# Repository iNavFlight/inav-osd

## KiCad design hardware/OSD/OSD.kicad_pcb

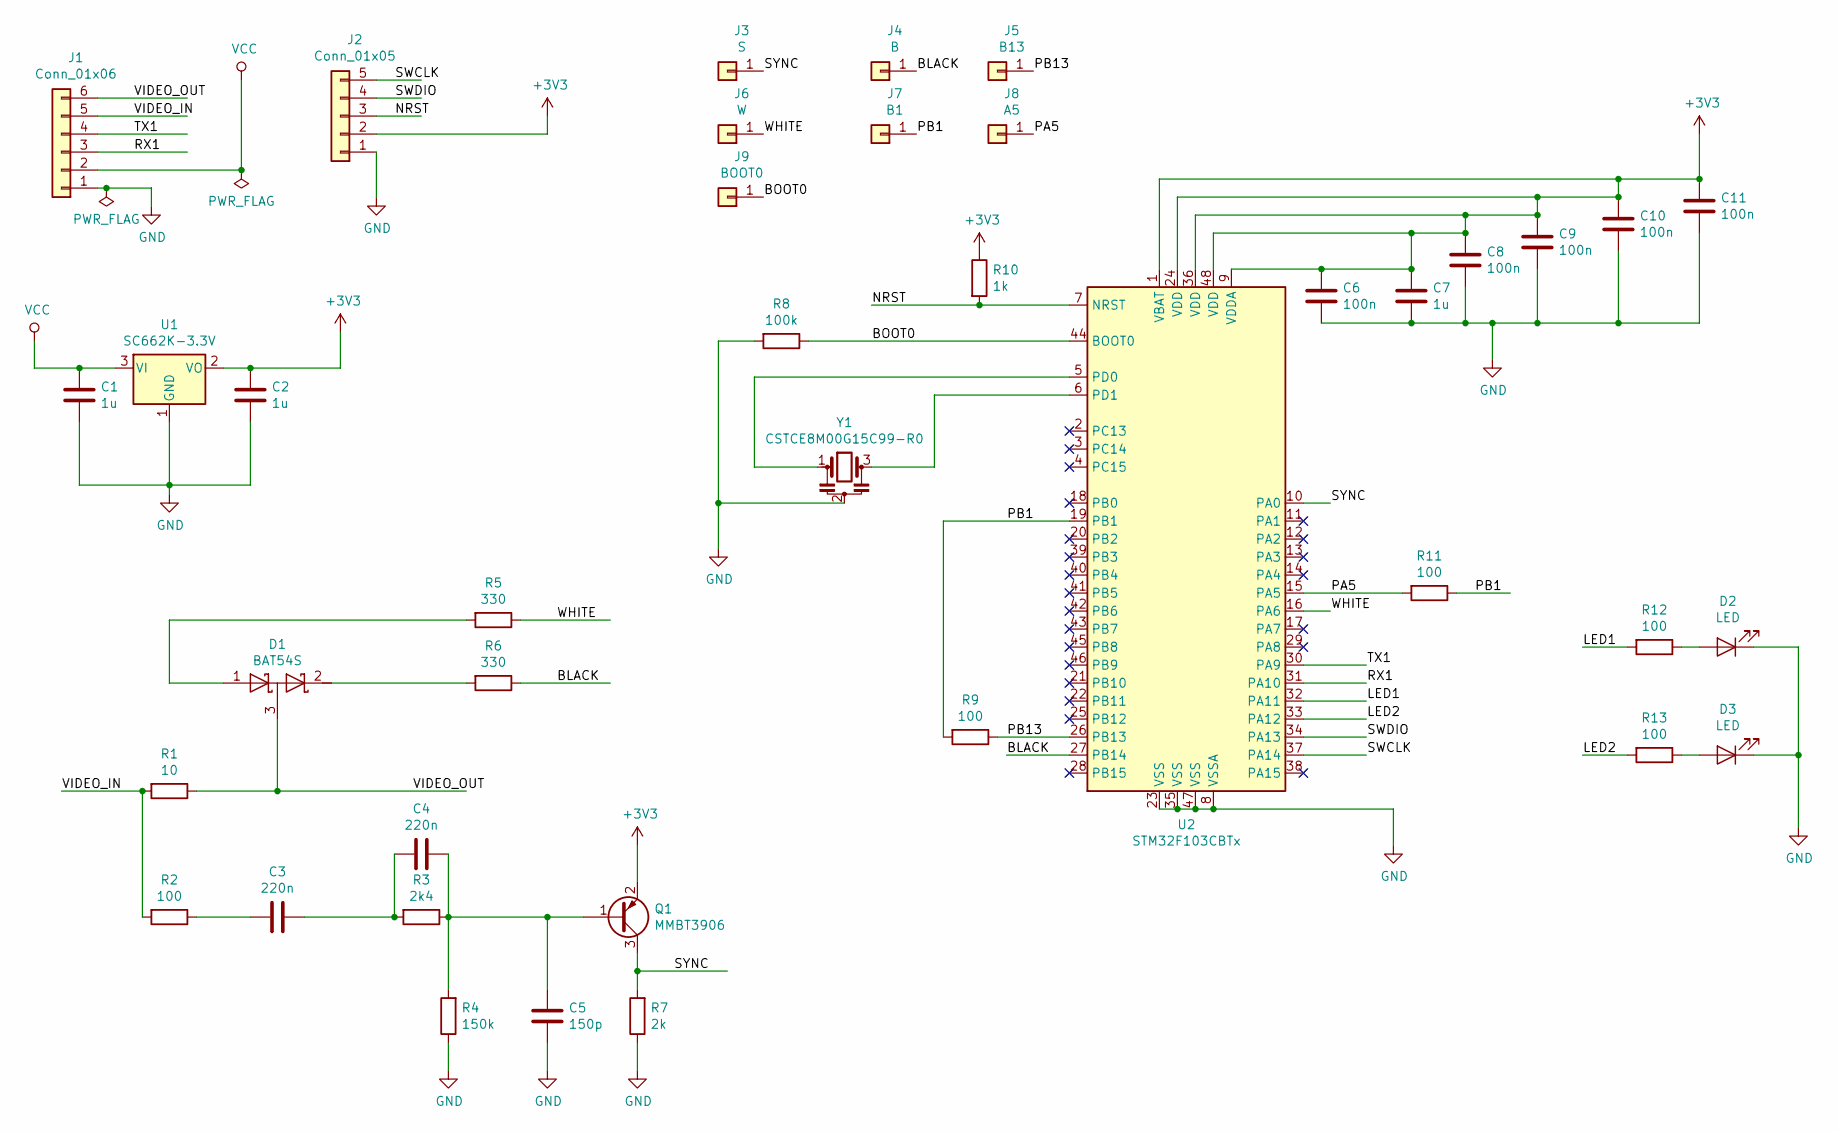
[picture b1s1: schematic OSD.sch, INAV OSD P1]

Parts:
C1, C2, C7: 1u; C_0603_1608Metric_Pad1.05x0.95mm_HandSolder
C3, C4: 220n; C_0603_1608Metric_Pad1.05x0.95mm_HandSolder
C5: 150p; C_0603_1608Metric_Pad1.05x0.95mm_HandSolder
C6, C8, C9, C10, C11: 100n; C_0603_1608Metric_Pad1.05x0.95mm_HandSolder
D1: BAT54S; SOT-23_Handsoldering
D2, D3: LED; LED_0603_1608Metric_Pad1.05x0.95mm_HandSolder
J1: Conn_01x06; PinHeader_1x06_P2.54mm_Vertical
J2: Conn_01x05; PinHeader_SMD_1x05_P1.27mm_Vertical
J3: S; PinHeader_SMD_1x01_P1.27mm_Vertical
J4: B; PinHeader_SMD_1x01_P1.27mm_Vertical
J5: B13; PinHeader_SMD_1x01_P1.27mm_Vertical
J6: W; PinHeader_SMD_1x01_P1.27mm_Vertical
J7: B1; PinHeader_SMD_1x01_P1.27mm_Vertical
J8: A5; PinHeader_SMD_1x01_P1.27mm_Vertical
J9: BOOT0; PinHeader_SMD_1x01_P1.27mm_Vertical
Q1: MMBT3906; SOT-23_Handsoldering
R1: 10; R_0603_1608Metric_Pad1.05x0.95mm_HandSolder
R2, R9, R11, R12, R13: 100; R_0603_1608Metric_Pad1.05x0.95mm_HandSolder
R3: 2k4; R_0603_1608Metric_Pad1.05x0.95mm_HandSolder
R4: 150k; R_0603_1608Metric_Pad1.05x0.95mm_HandSolder
R5, R6: 330; R_0603_1608Metric_Pad1.05x0.95mm_HandSolder
R7: 2k; R_0603_1608Metric_Pad1.05x0.95mm_HandSolder
R8: 100k; R_0603_1608Metric_Pad1.05x0.95mm_HandSolder
R10: 1k; R_0603_1608Metric_Pad1.05x0.95mm_HandSolder
U1: SC662K-3.3V; SOT-23_Handsoldering
U2: STM32F103CBTx; LQFP-48_7x7mm_P0.5mm
Y1: CSTCE8M00G15C99-R0; Resonator_SMD_muRata_CSTxExxV-3Pin_3.0x1.1mm_HandSoldering

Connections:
+3V3: C2.1, C6.1, C7.1, C8.1, C9.1, C10.1, C11.1, J2.2, Q1.2 (E), R10.1, U1.2 (VO), U2.1 (VBAT), U2.9 (VDDA), U2.24 (VDD), U2.36 (VDD), U2.48 (VDD)
/BLACK: J4.1, R6.1, U2.27 (PB14)
/BOOT0: J9.1, R8.1, U2.44 (BOOT0)
/LED1: R12.2, U2.32 (PA11)
/LED2: R13.2, U2.33 (PA12)
/NRST: J2.3, R10.2, U2.7 (NRST)
/PA5: J8.1, R11.2, U2.15 (PA5)
/PB1: J7.1, R9.2, R11.1, U2.19 (PB1)
/PB13: J5.1, R9.1, U2.26 (PB13)
/RX1: J1.3, U2.31 (PA10)
/SWCLK: J2.5, U2.37 (PA14)
/SWDIO: J2.4, U2.34 (PA13)
/SYNC: J3.1, Q1.3 (C), R7.2, U2.10 (PA0)
/TX1: J1.4, U2.30 (PA9)
/VIDEO_IN: J1.5, R1.2, R2.2
/VIDEO_OUT: D1.3 (common), J1.6, R1.1
/WHITE: J6.1, R5.1, U2.16 (PA6)
GND: C1.2, C2.2, C5.2, C6.2, C7.2, C8.2, C9.2, C10.2, C11.2, D2.1 (K), D3.1 (K), J1.1, J2.1, R4.1, R7.1, R8.2, U1.1 (GND), U2.8 (VSSA), U2.23 (VSS), U2.35 (VSS), U2.47 (VSS), Y1.2
unnamed: C3.1, R2.1
unnamed: C3.2, C4.1, R3.2
unnamed: C4.2, C5.1, Q1.1 (B), R3.1, R4.2
unnamed: D1.1 (A), R5.2
unnamed: D1.2 (K), R6.2
unnamed: D2.2 (A), R12.1
unnamed: D3.2 (A), R13.1
unnamed: U2.5 (PD0), Y1.1
unnamed: U2.6 (PD1), Y1.3
VCC: C1.1, J1.2, U1.3 (VI)

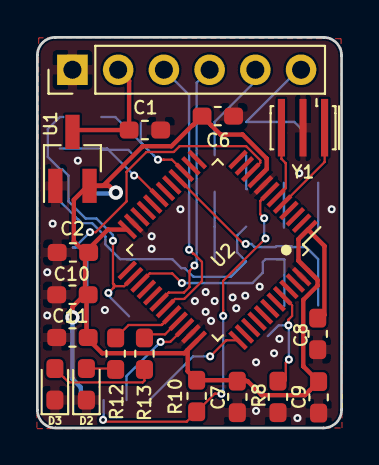
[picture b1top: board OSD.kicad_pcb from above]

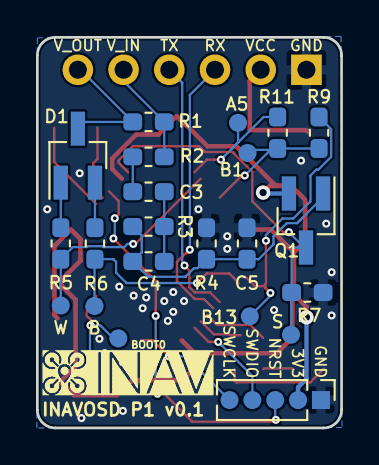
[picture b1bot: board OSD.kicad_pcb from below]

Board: 2 copper layers, 16.9 x 21.7 mm, 41 parts (23 on the bottom side), 28 nets.

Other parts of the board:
LOGO: LOGO

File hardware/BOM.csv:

"Id";"Designator";"Package";"Quantity";"Designation";"Supplier and ref";
1;"LOGO";"LOGO";1;"";;;
2;"R3";"R_0603_1608Metric_Pad1.05x0.95mm_HandSolder";1;"2k4";;;
3;"C4,C3";"C_0603_1608Metric_Pad1.05x0.95mm_HandSolder";2;"220n";;;
4;"C10,C8,C9,C11,C6";"C_0603_1608Metric_Pad1.05x0.95mm_HandSolder";5;"100n";;;
5;"C1,C2,C7";"C_0603_1608Metric_Pad1.05x0.95mm_HandSolder";3;"1u";;;
6;"C5";"C_0603_1608Metric_Pad1.05x0.95mm_HandSolder";1;"150p";;;
7;"D1";"SOT-23_Handsoldering";1;"BAT54S";;;
8;"J1";"PinHeader_1x06_P2.54mm_Vertical";1;"Conn_01x06";;;
9;"Q1";"SOT-23_Handsoldering";1;"MMBT3906";;;
10;"R1";"R_0603_1608Metric_Pad1.05x0.95mm_HandSolder";1;"10";;;
11;"R2,R11,R9,R12,R13";"R_0603_1608Metric_Pad1.05x0.95mm_HandSolder";5;"100";;;
12;"R4";"R_0603_1608Metric_Pad1.05x0.95mm_HandSolder";1;"150k";;;
13;"R5,R6";"R_0603_1608Metric_Pad1.05x0.95mm_HandSolder";2;"330";;;
14;"R7";"R_0603_1608Metric_Pad1.05x0.95mm_HandSolder";1;"2k";;;
15;"R8";"R_0603_1608Metric_Pad1.05x0.95mm_HandSolder";1;"100k";;;
16;"R10";"R_0603_1608Metric_Pad1.05x0.95mm_HandSolder";1;"1k";;;
17;"U1";"SOT-23_Handsoldering";1;"SC662K-3.3V";;;
18;"U2";"LQFP-48_7x7mm_P0.5mm";1;"STM32F103CBTx";;;
19;"Y1";"Resonator_SMD_muRata_CSTxExxV-3Pin_3.0x1.1mm_HandSoldering";1;"CSTCE8M00G15C99-R0";;;
20;"J2";"PinHeader_SMD_1x05_P1.27mm_Vertical";1;"Conn_01x05";;;
21;"J3";"PinHeader_SMD_1x01_P1.27mm_Vertical";1;"S";;;
22;"J4";"PinHeader_SMD_1x01_P1.27mm_Vertical";1;"B";;;
23;"J5";"PinHeader_SMD_1x01_P1.27mm_Vertical";1;"B13";;;
24;"J6";"PinHeader_SMD_1x01_P1.27mm_Vertical";1;"W";;;
25;"J7";"PinHeader_SMD_1x01_P1.27mm_Vertical";1;"B1";;;
26;"J8";"PinHeader_SMD_1x01_P1.27mm_Vertical";1;"A5";;;
27;"J9";"PinHeader_SMD_1x01_P1.27mm_Vertical";1;"BOOT0";;;
28;"D2,D3";"LED_0603_1608Metric_Pad1.05x0.95mm_HandSolder";2;"LED";;;

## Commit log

2019-02-08 Version 0.1 of the OSD P1 PCB
2019-02-09 Add a couple of leds
    They could be useful for signaling status and/or errors
2019-02-12 Change BLACK and WHITE resistors to 330
    4k7 makes the OSD too faint
